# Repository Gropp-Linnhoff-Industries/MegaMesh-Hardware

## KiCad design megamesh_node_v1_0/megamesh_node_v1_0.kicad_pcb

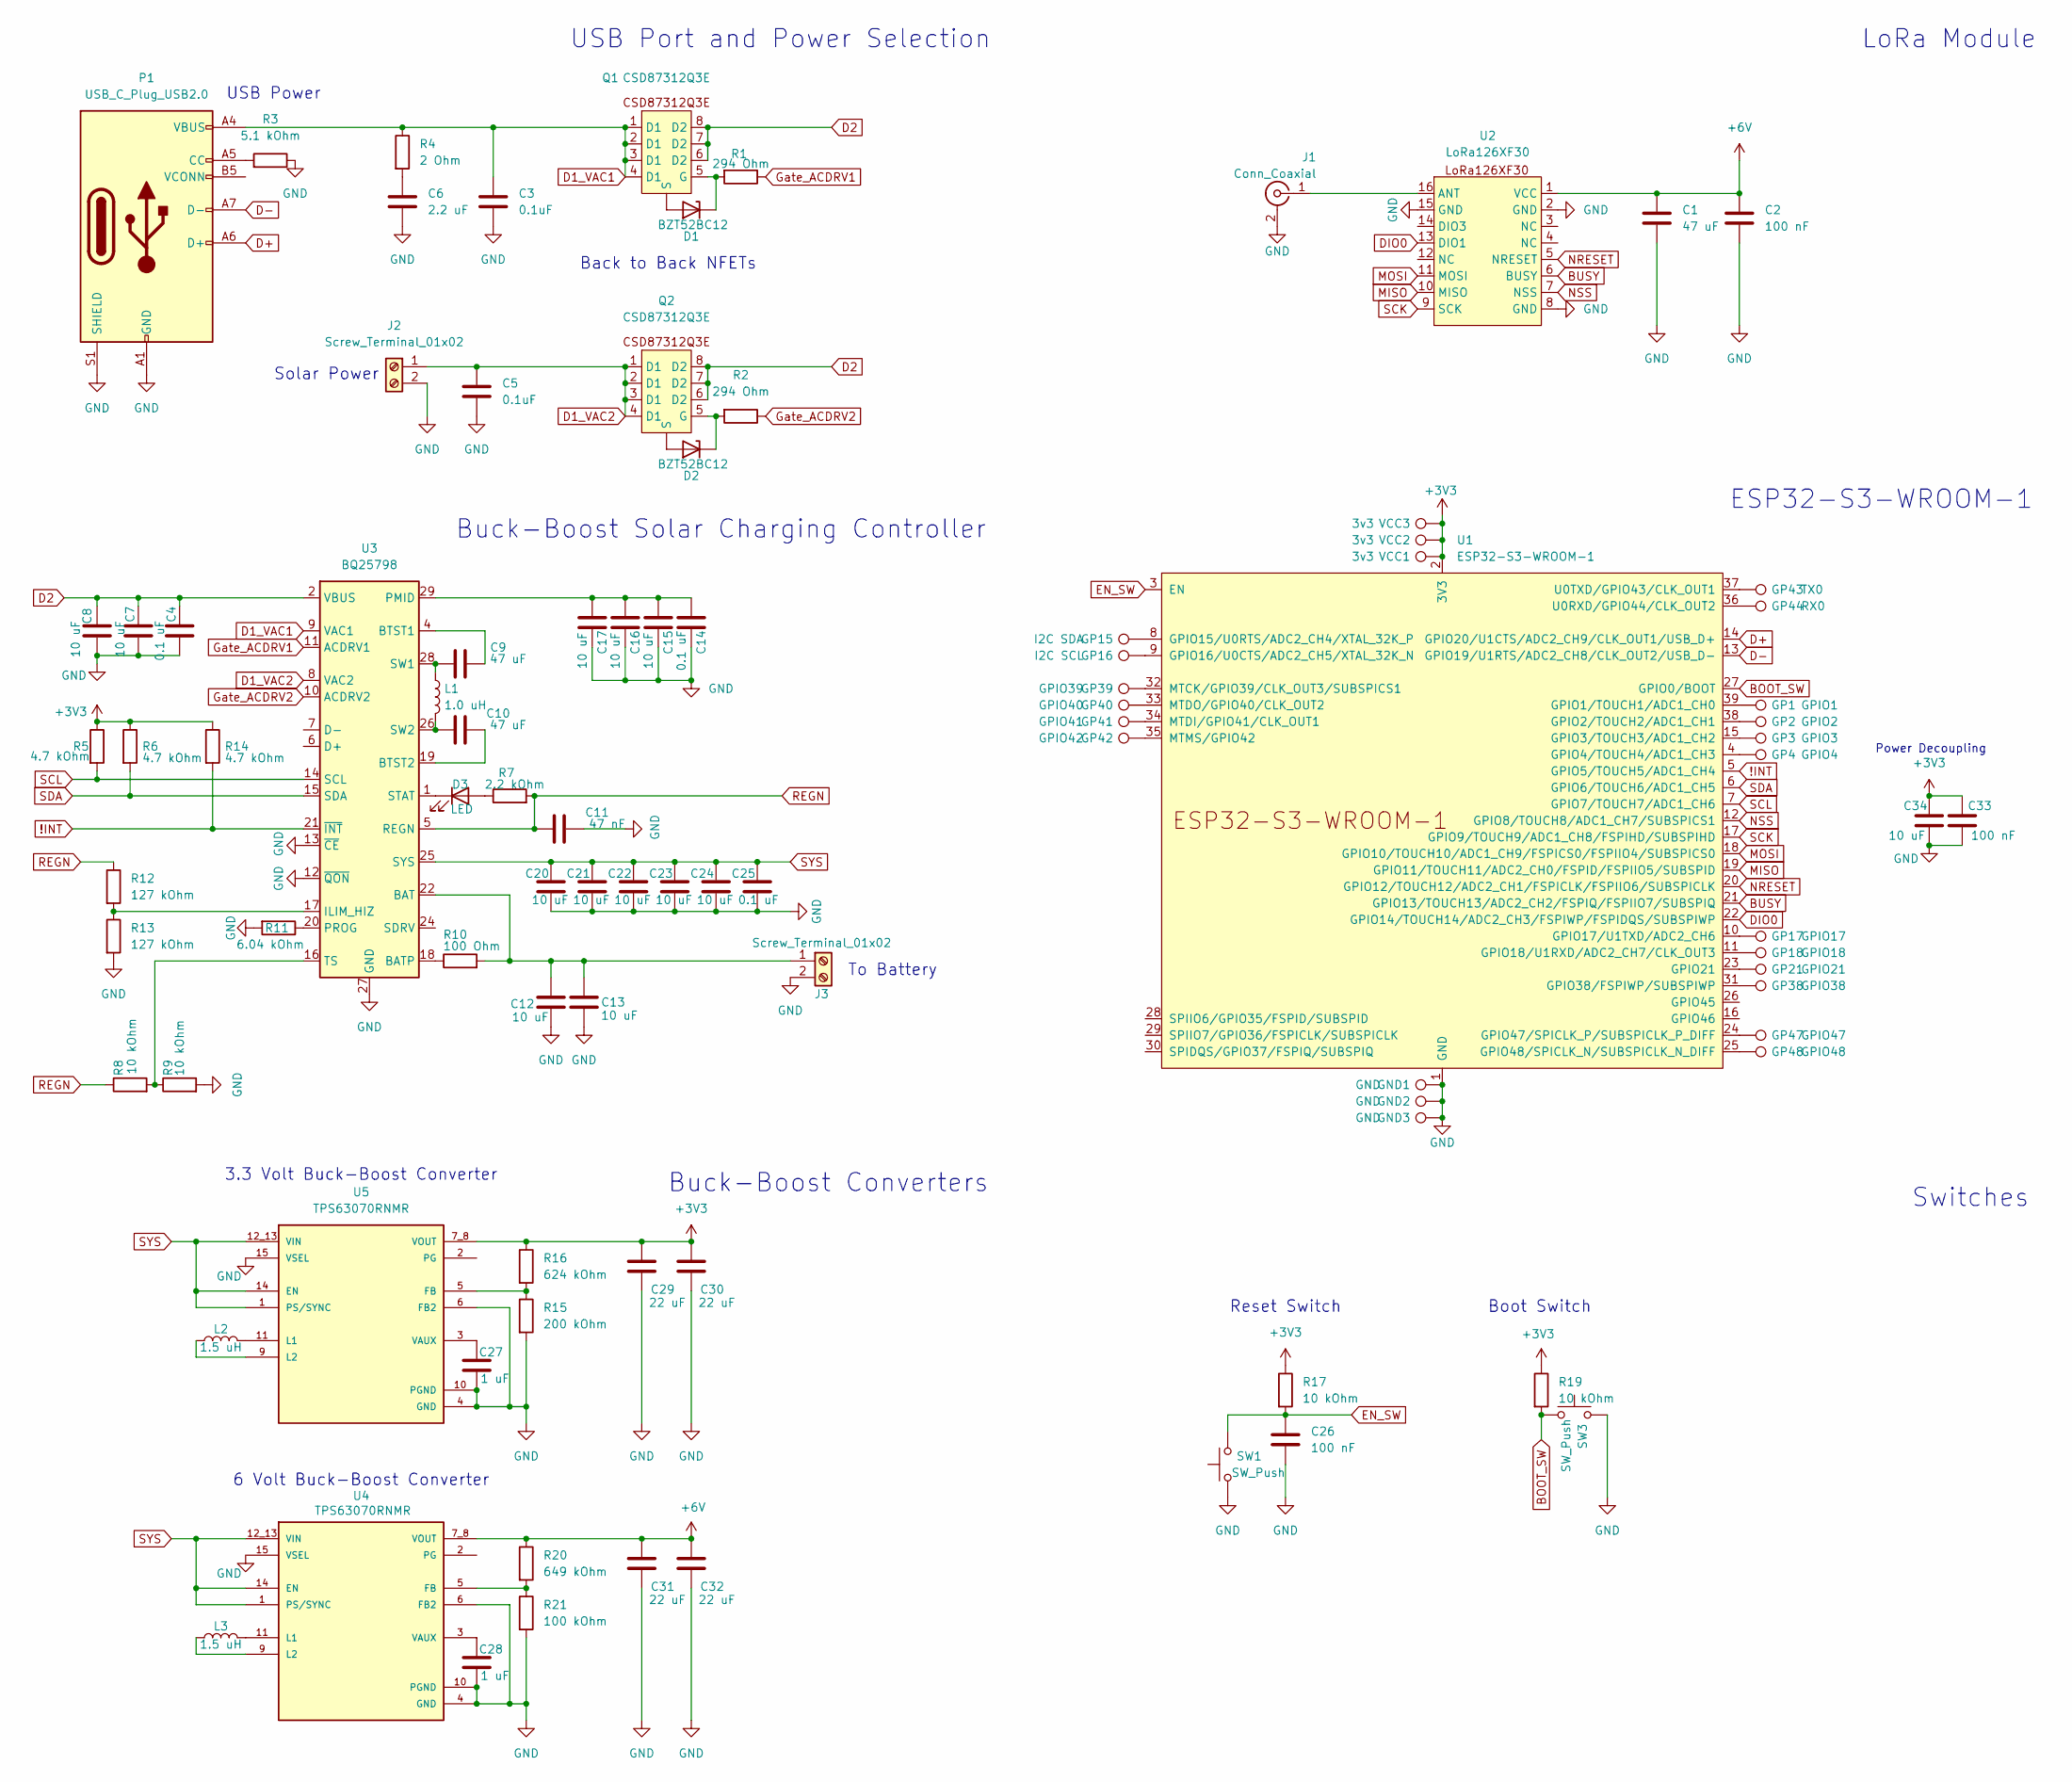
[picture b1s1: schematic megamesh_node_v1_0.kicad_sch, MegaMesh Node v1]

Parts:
C1, C9, C10: 47 uF; C_1206_3216Metric
C2, C26, C33: 100 nF; C_0603_1608Metric
C3, C5: 0.1uF; C_0603_1608Metric
C4, C14, C25: 0.1 uF; C_0603_1608Metric
C6: 2.2 uF; C_0603_1608Metric
C7, C8, C12, C13, C15, C16, C17, C20, C21, C22, C23, C24, C34: 10 uF; C_0805_2012Metric
C11: 47 nF; C_0603_1608Metric
C27, C28: 1 uF; C_0603_1608Metric
C29, C30, C31, C32: 22 uF; C_0805_2012Metric
D1, D2: BZT52BC12; D_SOD-123F
D3: LED; LED-SMD_L1.7-W0.6-R-RD
GND1, GND2, GND3: GND; TestPoint_THTPad_2.0x2.0mm_Drill1.0mm
GP1: GPIO1; TestPoint_THTPad_D2.0mm_Drill1.0mm
GP2: GPIO2; TestPoint_THTPad_D2.0mm_Drill1.0mm
GP3: GPIO3; TestPoint_THTPad_D2.0mm_Drill1.0mm
GP4: GPIO4; TestPoint_THTPad_D2.0mm_Drill1.0mm
GP15: I2C SDA; TestPoint_THTPad_D2.0mm_Drill1.0mm
GP16: I2C SCL; TestPoint_THTPad_D2.0mm_Drill1.0mm
GP17: GPIO17; TestPoint_THTPad_D2.0mm_Drill1.0mm
GP18: GPIO18; TestPoint_THTPad_D2.0mm_Drill1.0mm
GP21: GPIO21; TestPoint_THTPad_D2.0mm_Drill1.0mm
GP38: GPIO38; TestPoint_THTPad_D2.0mm_Drill1.0mm
GP39: GPIO39; TestPoint_THTPad_D2.0mm_Drill1.0mm
GP40: GPIO40; TestPoint_THTPad_D2.0mm_Drill1.0mm
GP41: GPIO41; TestPoint_THTPad_D2.0mm_Drill1.0mm
GP42: GPIO42; TestPoint_THTPad_D2.0mm_Drill1.0mm
GP43: TX0; TestPoint_THTPad_D2.0mm_Drill1.0mm
GP44: RX0; TestPoint_THTPad_D2.0mm_Drill1.0mm
GP47: GPIO47; TestPoint_THTPad_D2.0mm_Drill1.0mm
GP48: GPIO48; TestPoint_THTPad_D2.0mm_Drill1.0mm
J1: Conn_Coaxial; SMA_BAT_Wireless_BWSMA-KWE-Z001
J2, J3: Screw_Terminal_01x02; CONN-TH_2P-P3.81_KF124-3.81-2P
L1: 1.0 uH; IND-SMD_L7.1-W6.5-P5.60
L2, L3: 1.5 uH; IND-SMD_L4.2-W4.0_SPM4030T
P1: USB_C_Plug_USB2.0; USB_C_Receptacle_HRO_TYPE-C-31-M-12
Q1, Q2: CSD87312Q3E; SON 3.3x3.3mm
R1, R2: 294 Ohm; C_0603_1608Metric
R3: 5.1 kOhm; C_0603_1608Metric
R4: 2 Ohm; C_0603_1608Metric
R5, R6, R14: 4.7 kOhm; C_0603_1608Metric
R7: 2.2 kOhm; C_0603_1608Metric
R8, R9, R17, R19: 10 kOhm; C_0603_1608Metric
R10: 100 Ohm; C_0603_1608Metric
R11: 6.04 kOhm; C_0603_1608Metric
R12, R13: 127 kOhm; C_0603_1608Metric
R15: 200 kOhm; C_0603_1608Metric
R16: 624 kOhm; C_0603_1608Metric
R20: 649 kOhm; C_0603_1608Metric
R21: 100 kOhm; C_0603_1608Metric
SW1, SW3: SW_Push; SW_TS-1088-AR02016
U1: ESP32-S3-WROOM-1
U2: LoRa126XF30
U3: BQ25798; Texas_RQM0029A_VQFN-29_4x4mm_P0.4mm
U4, U5: TPS63070RNMR; VREG_TPS63070RNMR; PARTREV B
VCC1, VCC2, VCC3: 3v3; TestPoint_THTPad_D2.0mm_Drill1.0mm

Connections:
!INT: R14.2, U1.5 (GPIO5/TOUCH5/ADC1_CH4), U3.21 (~INT)
+3V3: C29.1, C30.1, C33.1, C34.1, R5.1, R6.1, R14.1, R16.1, R17.1, R19.1, U1.2 (3V3), U5.7_8 (VOUT), VCC1.1, VCC2.1, VCC3.1
+6V: C1.1, C2.1, C31.1, C32.1, R20.1, U2.1 (VCC), U4.7_8 (VOUT)
BOOT_SW: R19.2, SW3.1, U1.27 (GPIO0/BOOT)
BUSY: U1.21 (GPIO13/TOUCH13/ADC2_CH2/FSPIQ/FSPIIO7/S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), U2.6 (BUSY)
D1_VAC1: C3.1, P1.A4 (VBUS), P1.A9 (VBUS), P1.B4 (VBUS), P1.B9 (VBUS), Q1.1 (D1), Q1.2 (D1), Q1.3 (D1), Q1.4 (D1), R4.1, U3.9 (VAC1)
D1_VAC2: C5.1, J2.1, Q2.1 (D1), Q2.2 (D1), Q2.3 (D1), Q2.4 (D1), U3.8 (VAC2)
D2: C4.1, C7.1, C8.1, Q1.6 (D2), Q1.7 (D2), Q1.8 (D2), Q2.6 (D2), Q2.7 (D2), Q2.8 (D2), U3.2 (VBUS), U3.3 (VBUS)
D+: P1.A6 (D+), U1.14 (GPIO20/U1CTS/ADC2_CH9/CLK_OUT1/USB_D+)
D-: P1.A7 (D-), U1.13 (GPIO19/U1RTS/ADC2_CH8/CLK_OUT2/USB_D-)
DIO0: U1.22 (GPIO14/TOUCH14/ADC2_CH3/FSPIWP/FSPIDQS/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), U2.13 (DIO1)
EN_SW: C26.1, R17.2, SW1.2, U1.3 (EN)
GND: C1.2, C2.2, C3.2, C4.2, C5.2, C6.2, C7.2, C8.2, C11.1, C12.2, C13.2, C14.1, C15.1, C16.1, C17.1, C20.2, C21.2, C22.2, C23.2, C24.2, C25.2, C26.2, C27.2, C28.2, C29.2, C30.2, C31.2, C32.2, C33.2, C34.2, GND1.1, GND2.1, GND3.1, J1.2 (Ext), J2.2, J3.2, P1.A1 (GND), P1.A12 (GND), P1.B1 (GND), P1.B12 (GND), P1.S1 (SHIELD), R3.1, R9.2, R11.2, R13.2, R15.2, R21.2, SW1.1, SW3.2, U1.1 (GND), U1.40 (GND), U1.41 (GND), U2.2 (GND), U2.8 (GND), U2.15 (GND), U3.12 (~QON), U3.13 (~CE), U3.27 (GND), U4.4 (GND), U4.6 (FB2), U4.10 (PGND), U4.15 (VSEL), U5.4 (GND), U5.6 (FB2), U5.10 (PGND), U5.15 (VSEL)
Gate_ACDRV1: R1.1, U3.11 (ACDRV1)
Gate_ACDRV2: R2.1, U3.10 (ACDRV2)
MISO: U1.19 (GPIO11/TOUCH11/ADC2_CH0/FSPID/FSPIIO5/S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), U2.10 (MISO)
MOSI: U1.18 (GPIO10/TOUCH10/ADC1_CH9/FSPICS0/FSPIIO4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), U2.11 (MOSI)
NRESET: U1.20 (GPIO12/TOUCH12/ADC2_CH1/FSPICLK/FSPIIO6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), U2.5 (NRESET)
NSS: U1.12 (GPIO8/TOUCH8/ADC1_CH7/SUBSPICS1), U2.7 (NSS)
unnamed: C6.1, R4.2
unnamed: D1.2 (A), Q1. (S), Q1.9
unnamed: D1.1 (K), Q1.5 (G), R1.2
unnamed: D2.2 (A), Q2. (S), Q2.9
unnamed: D2.1 (K), Q2.5 (G), R2.2
unnamed: D3.2 (A), R7.1
unnamed: D3.1 (K), U3.1 (STAT)
unnamed: J1.1 (In), U2.16 (ANT)
unnamed: C12.1, C13.1, J3.1, R10.2, U3.22 (BAT), U3.23 (BAT)
unnamed: P1.A5 (CC), R3.2
unnamed: GP1.1, U1.39 (GPIO1/TOUCH1/ADC1_CH0)
unnamed: GP2.1, U1.38 (GPIO2/TOUCH2/ADC1_CH1)
unnamed: GP3.1, U1.15 (GPIO3/TOUCH3/ADC1_CH2)
unnamed: GP4.1, U1.4 (GPIO4/TOUCH4/ADC1_CH3)
unnamed: GP15.1, U1.8 (GPIO15/U0RTS/ADC2_CH4/XTAL_32K_P)
unnamed: GP16.1, U1.9 (GPIO16/U0CTS/ADC2_CH5/XTAL_32K_N)
unnamed: GP17.1, U1.10 (GPIO17/U1TXD/ADC2_CH6)
unnamed: GP18.1, U1.11 (GPIO18/U1RXD/ADC2_CH7/CLK_OUT3)
unnamed: GP21.1, U1.23 (GPIO21)
unnamed: GP38.1, U1.31 (GPIO38/FSPIWP/SUBSPIWP)
unnamed: GP47.1, U1.24 (GPIO47/SPICLK_P/SUBSPICLK_P_DIFF)
unnamed: GP48.1, U1.25 (GPIO48/SPICLK_N/SUBSPICLK_N_DIFF)
unnamed: GP39.1, U1.32 (MTCK/GPIO39/CLK_OUT3/SUBSPICS1)
unnamed: GP41.1, U1.34 (MTDI/GPIO41/CLK_OUT1)
unnamed: GP40.1, U1.33 (MTDO/GPIO40/CLK_OUT2)
unnamed: GP42.1, U1.35 (MTMS/GPIO42)
unnamed: GP44.1, U1.36 (U0RXD/GPIO44/CLK_OUT2)
unnamed: GP43.1, U1.37 (U0TXD/GPIO43/CLK_OUT1)
unnamed: R10.1, U3.18 (BATP)
unnamed: C9.1, U3.4 (BTST1)
unnamed: C10.1, U3.19 (BTST2)
unnamed: R12.2, R13.1, U3.17 (ILIM_HIZ)
unnamed: C14.2, C15.2, C16.2, C17.2, U3.29 (PMID)
unnamed: R11.1, U3.20 (PROG)
unnamed: C9.2, L1.1, U3.28 (SW1)
unnamed: C10.2, L1.2, U3.26 (SW2)
unnamed: R8.2, R9.1, U3.16 (TS)
unnamed: R20.2, R21.1, U4.5 (FB)
unnamed: L3.2, U4.11 (L1)
unnamed: L3.1, U4.9 (L2)
unnamed: C28.1, U4.3 (VAUX)
unnamed: R15.1, R16.2, U5.5 (FB)
unnamed: L2.2, U5.11 (L1)
unnamed: L2.1, U5.9 (L2)
unnamed: C27.1, U5.3 (VAUX)
REGN: C11.2, R7.2, R8.1, R12.1, U3.5 (REGN)
SCK: U1.17 (GPIO9/TOUCH9/ADC1_CH8/FSPIHD/SUBSPIHD), U2.9 (SCK)
SCL: R5.2, U1.7 (GPIO7/TOUCH7/ADC1_CH6), U3.14 (SCL)
SDA: R6.2, U1.6 (GPIO6/TOUCH6/ADC1_CH5), U3.15 (SDA)
SYS: C20.1, C21.1, C22.1, C23.1, C24.1, C25.1, U3.25 (SYS), U4.1 (PS/SYNC), U4.12_13 (VIN), U4.14 (EN), U5.1 (PS/SYNC), U5.12_13 (VIN), U5.14 (EN)

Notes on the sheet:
Back to Back NFETs
Solar Power
Buck-Boost Solar Charging Controller
Buck-Boost Converters
USB Port and Power Selection
Switches
6 Volt Buck-Boost Converter
To Battery
Boot Switch
Power Decoupling
LoRa Module
USB Power
ESP32-S3-WROOM-1
3.3 Volt Buck-Boost Converter
Reset Switch

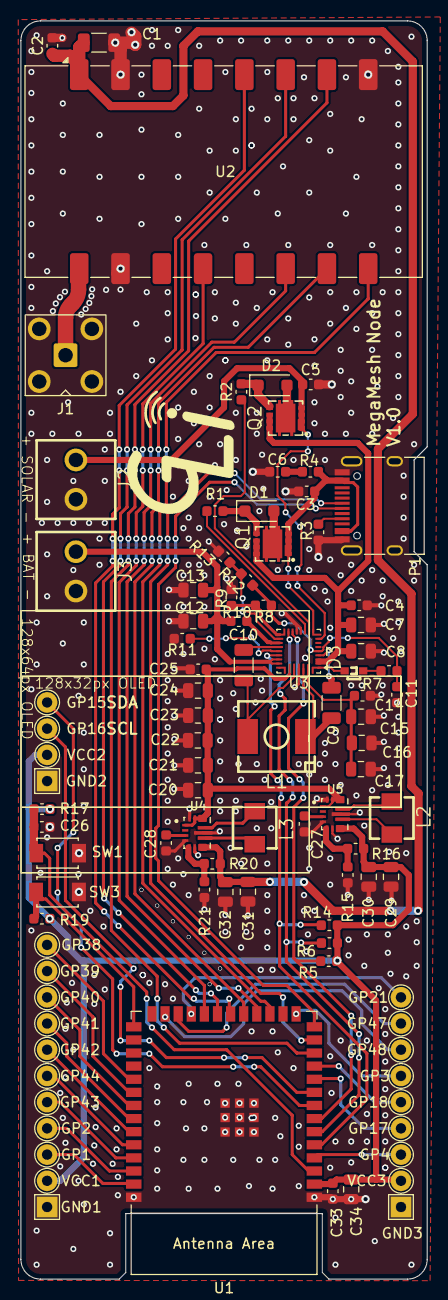
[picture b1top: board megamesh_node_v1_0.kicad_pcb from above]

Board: 2 copper layers, 39.4 x 121.9 mm, 95 parts (0 on the bottom side), 69 nets.

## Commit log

2026-03-18 Entwicklung Schaltplan und Platine
    Es geht voran
2026-03-19 Add image to README.md
2026-03-19 Fertigstellung
    I guess
